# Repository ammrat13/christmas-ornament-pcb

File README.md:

# EE 256 Final Project: Christmas Ornament

Board files and firmware for my final project for EE 256. I made a relatively
simple project - just a smart christmas ornament.

  * Low-light conditions turn on the LEDs
  * Shaking the ornament flashes the NeoPixels
  * Thresholds and flash parameters configurable via micro-SD card
  * Sensor values, activation statistics, and device health visible over
    Bluetooth LE
  * Supports LiIon batteries
  * Watchdog timer for reliability

## Block Diagram

## Project Structure
  * `firmware`: code for the MCU
  * `host`: code to communicate with the MCU over Bluetooth LE
  * `kicad`: board files
  * `kicad-lib`: global library files referenced by the board files

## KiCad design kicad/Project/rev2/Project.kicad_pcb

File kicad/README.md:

# PCB Files

This folder has the KiCad files for the PCBs fabricated. The ADXL 343 Adapter
and Revision 1 of the Project were fabricated. The files in the `kicad-lib`
folder may be needed to edit these files.

## Errata

### Project Revision 1
  * Q1 uses the incorrect footprint. They should be rotated 120 degrees
    counter-clockwise.
  * D2 and D3 don't have decoupling capacitors. They should have 1uF capacitors.
  * D2 doesn't have a decoupling resistor on the data line. It should have a
    470R on the input.

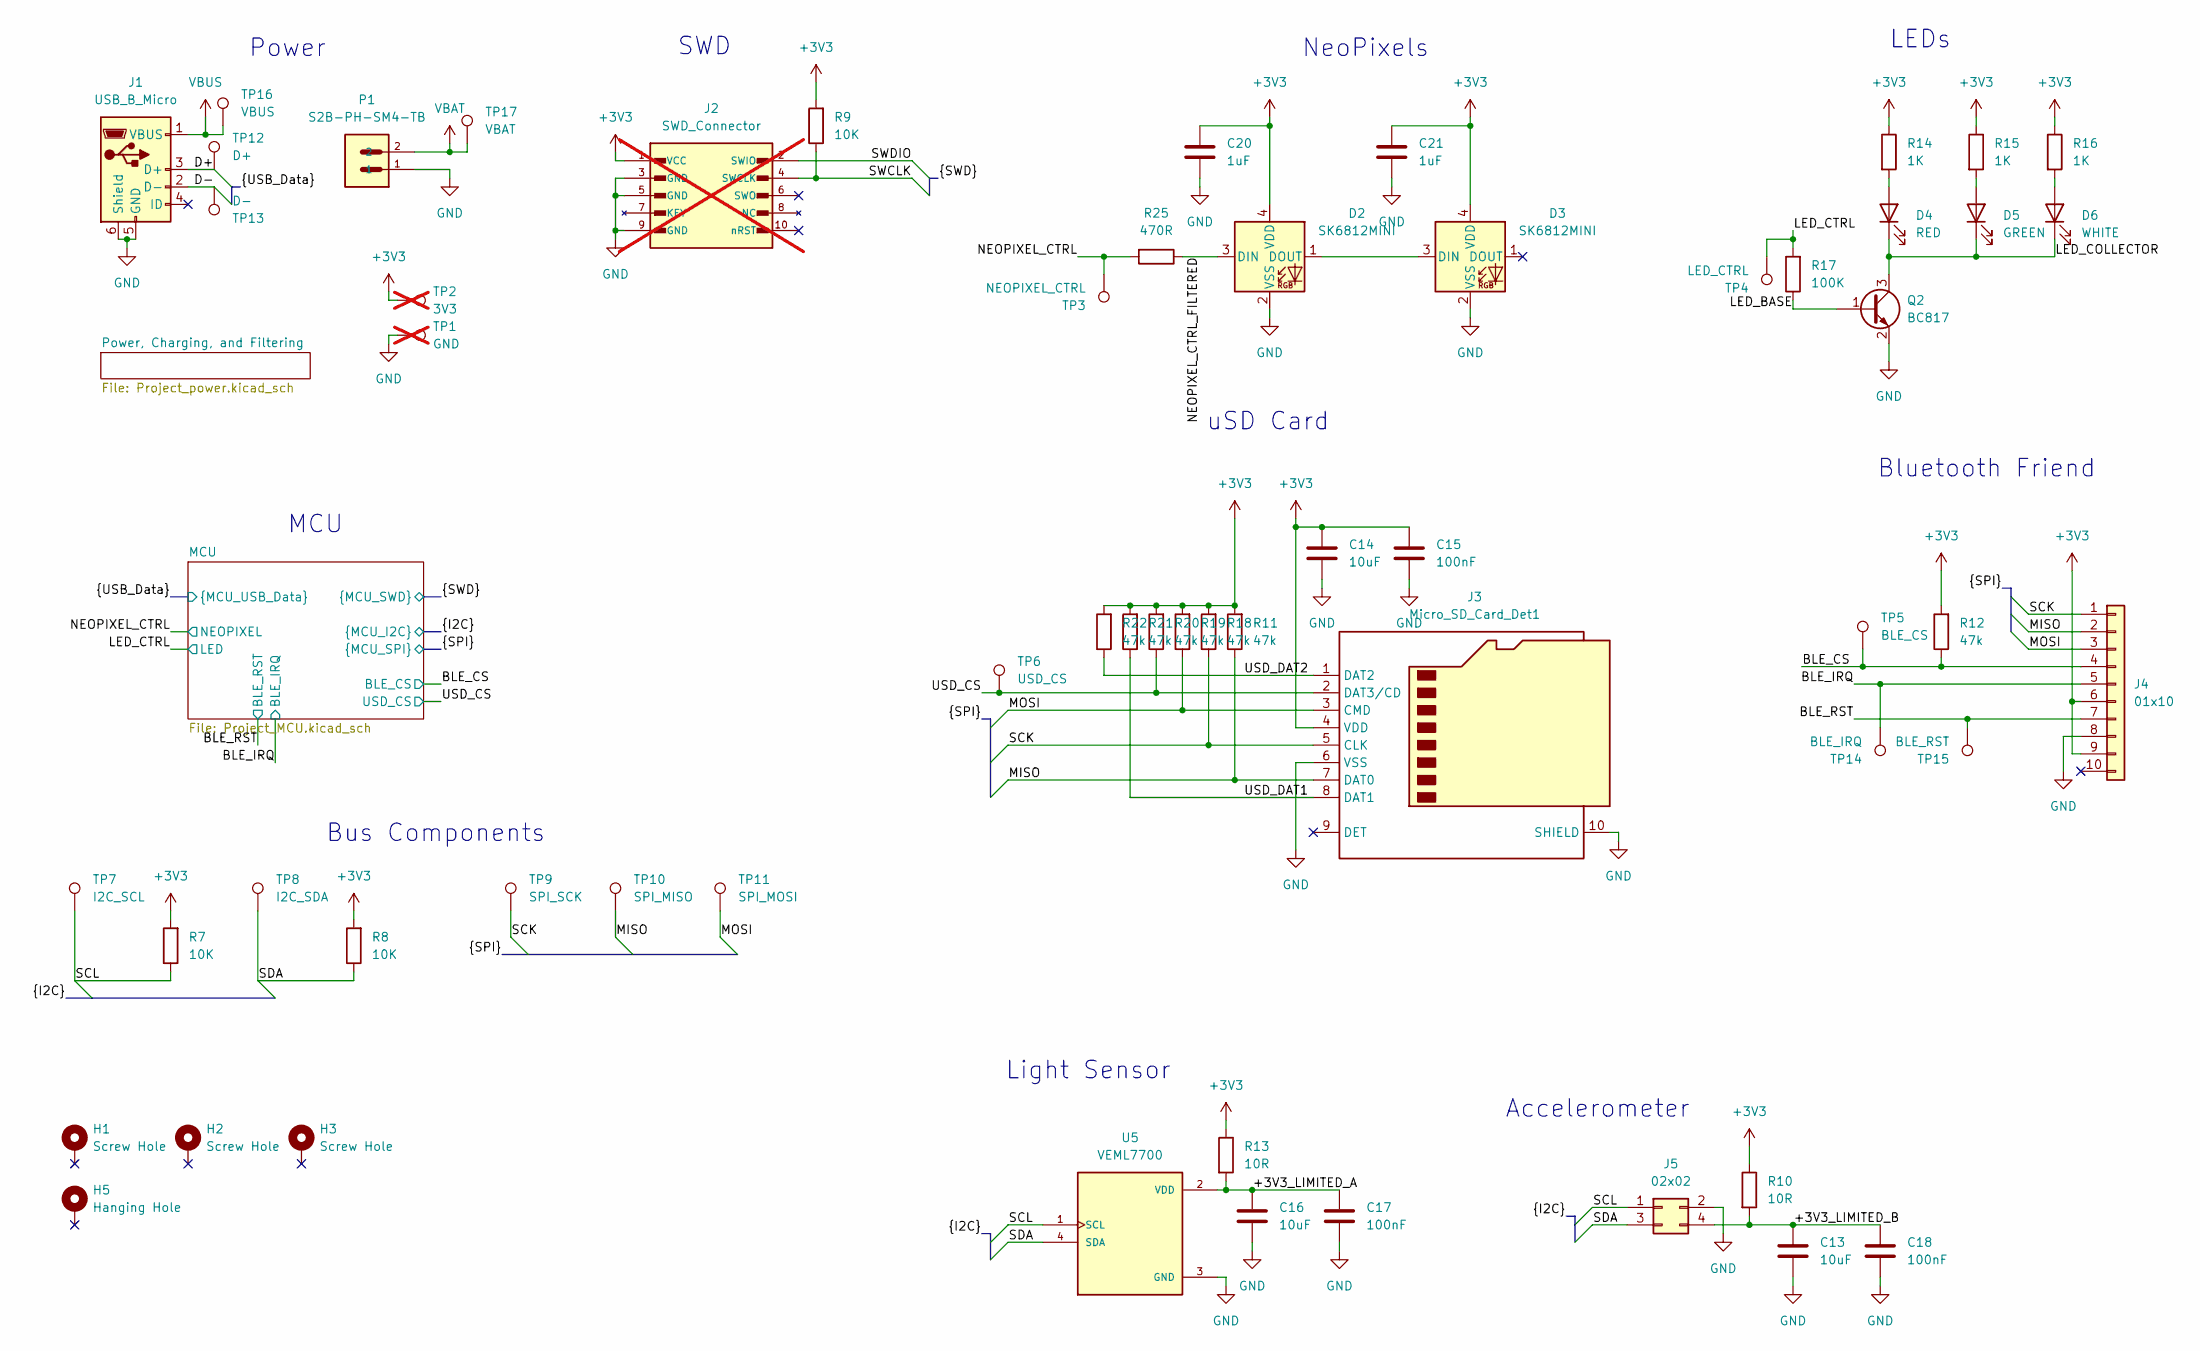
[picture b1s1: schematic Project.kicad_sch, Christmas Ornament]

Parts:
C13, C14, C16: 10uF; C_0805_2012Metric_Pad1.18x1.45mm_HandSolder; Mfr P/N CL21A106KOQNNNE
C15, C17, C18: 100nF; C_0402_1005Metric_Pad0.74x0.62mm_HandSolder; Mfr P/N CL05B104KP5NNNC
C20, C21: 1uF; C_0603_1608Metric_Pad1.08x0.95mm_HandSolder; Mfr P/N CC0603KRX7R7BB105
D2, D3: SK6812MINI; LED_SK6812MINI_PLCC4_3.5x3.5mm_P1.75mm; Mfr P/N 2659
D4: RED; LED_0805_2012Metric_Pad1.15x1.40mm_HandSolder; Mfr P/N LTST-S220KRKT
D5: GREEN; LED_0805_2012Metric_Pad1.15x1.40mm_HandSolder; Mfr P/N LTST-S220KGKT
D6: WHITE; LED_0805_2012Metric_Pad1.15x1.40mm_HandSolder; Mfr P/N LTW-170TK
H1, H2, H3: Screw Hole; MountingHole_3.2mm_M3_DIN965_Pad_TopBottom
H5: Hanging Hole; MountingHole_3.2mm_M3_DIN965_Pad_TopBottom
J1: USB_B_Micro; USB_Micro-B_Amphenol_10103594-0001LF_Horizontal; Mfr P/N 10103594-0001LF
J2: SWD_Connector; CNC_3220-10-0300-00; Mfr P/N 3220-10-0300-00; not fitted
J3: Micro_SD_Card_Det1; GCT_MEM2075-00-140-01-A; Mfr P/N MEM2075-00-140-01-A
J4: 01x10; PinSocket_1x10_P2.54mm_Vertical; Mfr P/N PPTC101LFBN-RC
J5: 02x02; PinSocket_2x02_P2.54mm_Vertical; Mfr P/N PPPC022LFBN-RC
P1: S2B-PH-SM4-TB; JST_PH_S2B-PH-SM4-TB_1x02-1MP_P2.00mm_Horizontal; Mfr P/N S2B-PH-SM4-TB
Q2: BC817; SOT-23; Mfr P/N BC817-25LT1G
R7, R8, R9: 10K; R_0603_1608Metric_Pad0.98x0.95mm_HandSolder; Mfr P/N RNCP0603FTD10K0
R10, R13: 10R; R_0603_1608Metric_Pad0.98x0.95mm_HandSolder; Mfr P/N RMCF0603FT10R0
R11, R12, R18, R19, R20, R21, R22: 47k; R_0603_1608Metric_Pad0.98x0.95mm_HandSolder; Mfr P/N RC0603FR-0747KL
R14, R15, R16: 1K; R_0603_1608Metric_Pad0.98x0.95mm_HandSolder; Mfr P/N MCT06030C1001FP500
R17: 100K; R_0603_1608Metric_Pad0.98x0.95mm_HandSolder; Mfr P/N RMCF0603FT100K
R25: 470R; R_0603_1608Metric_Pad0.98x0.95mm_HandSolder; Mfr P/N RC0603JR-07470RL
TP1: GND; TP_5011; Mfr P/N 5011; not fitted
TP2: 3V3; TP_5011; Mfr P/N 5010; not fitted
TP3: NEOPIXEL_CTRL; TestPoint_Pad_D2.0mm
TP4: LED_CTRL; TestPoint_Pad_D2.0mm
TP5: BLE_CS; TestPoint_Pad_D2.0mm
TP6: USD_CS; TestPoint_Pad_D2.0mm
TP7: I2C_SCL; TestPoint_Pad_D2.0mm
TP8: I2C_SDA; TestPoint_Pad_D2.0mm
TP9: SPI_SCK; TestPoint_Pad_D2.0mm
TP10: SPI_MISO; TestPoint_Pad_D2.0mm
TP11: SPI_MOSI; TestPoint_Pad_D2.0mm
TP12: D+; TestPoint_Pad_D2.0mm
TP13: D-; TestPoint_Pad_D2.0mm
TP14: BLE_IRQ; TestPoint_Pad_D2.0mm
TP15: BLE_RST; TestPoint_Pad_D2.0mm
TP16: VBUS; TestPoint_Pad_D2.0mm
TP17: VBAT; TestPoint_Pad_D2.0mm
U5: VEML7700; XDCR_VEML7700-TR; Mfr P/N VEML7700-TR

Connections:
+3V3: C14.1, C15.1, C20.1, C21.1, D2.4 (VDD), D3.4 (VDD), J2.1 (VCC), J3.4 (VDD), J4.6, J4.9, R7.2, R8.2, R9.2, R10.1, R11.2, R12.2, R13.1, R14.1, R15.1, R16.1, R18.2, R19.2, R20.2, R21.2, R22.2, TP2.1; also elsewhere on the board
/+3V3_LIMITED_A: C16.1, C17.1, R13.2, U5.2 (VDD)
/+3V3_LIMITED_B: C13.1, C18.1, J5.4, R10.2
/BLE_CS: J4.4, R12.1, TP5.1; also elsewhere on the board
/BLE_IRQ: J4.5, TP14.1; also elsewhere on the board
/BLE_RST: J4.7, TP15.1; also elsewhere on the board
/D+: J1.3 (D+), TP12.1; also elsewhere on the board
/D-: J1.2 (D-), TP13.1; also elsewhere on the board
/LED_BASE: Q2.1 (B), R17.1
/LED_COLLECTOR: D4.1 (K), D5.1 (K), D6.1 (K), Q2.3 (C)
/LED_CTRL: R17.2, TP4.1; also elsewhere on the board
/MISO: J3.7 (DAT0), J4.2, R11.1, TP10.1; also elsewhere on the board
/MOSI: J3.3 (CMD), J4.3, R19.1, TP11.1; also elsewhere on the board
/NEOPIXEL_CTRL: R25.2, TP3.1; also elsewhere on the board
/NEOPIXEL_CTRL_FILTERED: D2.3 (DIN), R25.1
/SCK: J3.5 (CLK), J4.1, R18.1, TP9.1; also elsewhere on the board
/SCL: J5.1, R7.1, TP7.1, U5.1 (SCL); also elsewhere on the board
/SDA: J5.3, R8.1, TP8.1, U5.4 (SDA); also elsewhere on the board
/SWCLK: J2.4 (SWCLK), R9.1; also elsewhere on the board
/SWDIO: J2.2 (SWIO); also elsewhere on the board
/USD_CS: J3.2 (DAT3/CD), R20.1, TP6.1; also elsewhere on the board
/USD_DAT1: J3.8 (DAT1), R21.1
/USD_DAT2: J3.1 (DAT2), R22.1
GND: C13.2, C14.2, C15.2, C16.2, C17.2, C18.2, C20.2, C21.2, D2.2 (VSS), D3.2 (VSS), J1.5 (GND), J1.6 (Shield), J2.3 (GND), J2.5 (GND), J2.9 (GND), J3.6 (VSS), J3.10 (SHIELD), J4.8, J5.2, P1.1, Q2.2 (E), TP1.1, U5.3 (GND); also elsewhere on the board
unnamed: D2.1 (DOUT), D3.3 (DIN)
unnamed: D4.2 (A), R14.2
unnamed: D5.2 (A), R15.2
unnamed: D6.2 (A), R16.2
VBAT: P1.2, TP17.1; also elsewhere on the board
VBUS: J1.1 (VBUS), TP16.1; also elsewhere on the board

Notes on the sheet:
MCU
Accelerometer
Bus Components
Bluetooth Friend
SWD
Light Sensor
NeoPixels
uSD Card
LEDs
Power

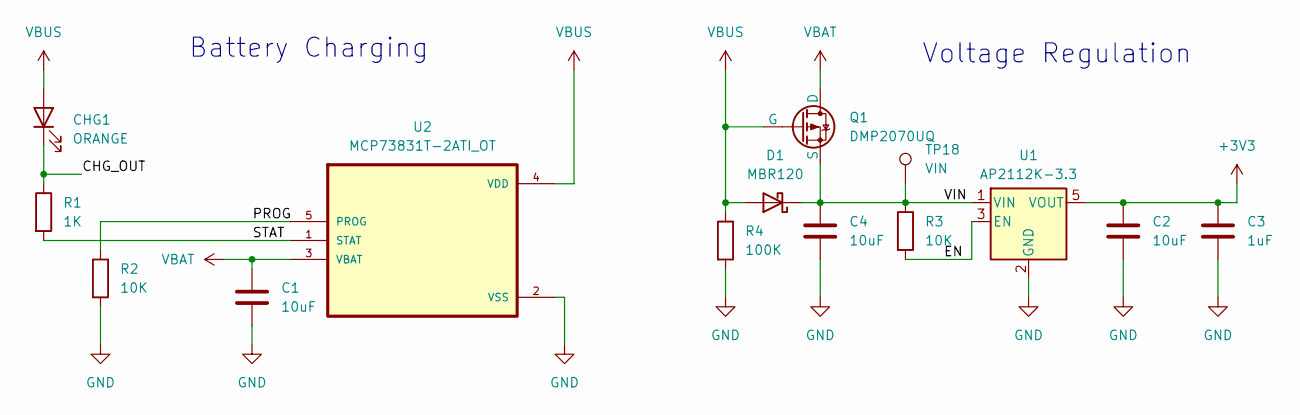
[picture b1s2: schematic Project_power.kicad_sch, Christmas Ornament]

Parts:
C1, C2, C4: 10uF; C_0805_2012Metric_Pad1.18x1.45mm_HandSolder; Mfr P/N CL21A106KOQNNNE
C3: 1uF; C_0603_1608Metric_Pad1.08x0.95mm_HandSolder; Mfr P/N CC0603KRX7R7BB105
CHG1: ORANGE; LED_0805_2012Metric_Pad1.15x1.40mm_HandSolder; Mfr P/N B1701UD--20D000414U1930
D1: MBR120; D_SOD-123; Mfr P/N MBR120LSFT1G
Q1: DMP2070UQ; SOT-23_Handsoldering
R1: 1K; R_0603_1608Metric_Pad0.98x0.95mm_HandSolder; Mfr P/N MCT06030C1001FP500
R2, R3: 10K; R_0603_1608Metric_Pad0.98x0.95mm_HandSolder; Mfr P/N RNCP0603FTD10K0
R4: 100K; R_0603_1608Metric_Pad0.98x0.95mm_HandSolder; Mfr P/N RMCF0603FT100K
TP18: VIN; TestPoint_Pad_D2.0mm
U1: AP2112K-3.3; SOT-23-5
U2: MCP73831T-2ATI_OT; SOT-23-5_HandSoldering; Mfr P/N MCP73831T-2ATI/OT

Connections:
+3V3: C2.1, C3.1, U1.5 (VOUT); also elsewhere on the board
/Power, Charging, and Filtering/CHG_OUT: CHG1.1 (K), R1.1
/Power, Charging, and Filtering/EN: R3.2, U1.3 (EN)
/Power, Charging, and Filtering/PROG: R2.1, U2.5 (PROG)
/Power, Charging, and Filtering/STAT: R1.2, U2.1 (STAT)
/Power, Charging, and Filtering/VIN: C4.1, D1.1 (K), Q1.2 (S), R3.1, TP18.1, U1.1 (VIN)
GND: C1.2, C2.2, C3.2, C4.2, R2.2, R4.2, U1.2 (GND), U2.2 (VSS); also elsewhere on the board
VBAT: C1.1, Q1.3 (D), U2.3 (VBAT); also elsewhere on the board
VBUS: CHG1.2 (A), D1.2 (A), Q1.1 (G), R4.1, U2.4 (VDD); also elsewhere on the board

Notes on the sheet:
Battery Charging
Voltage Regulation

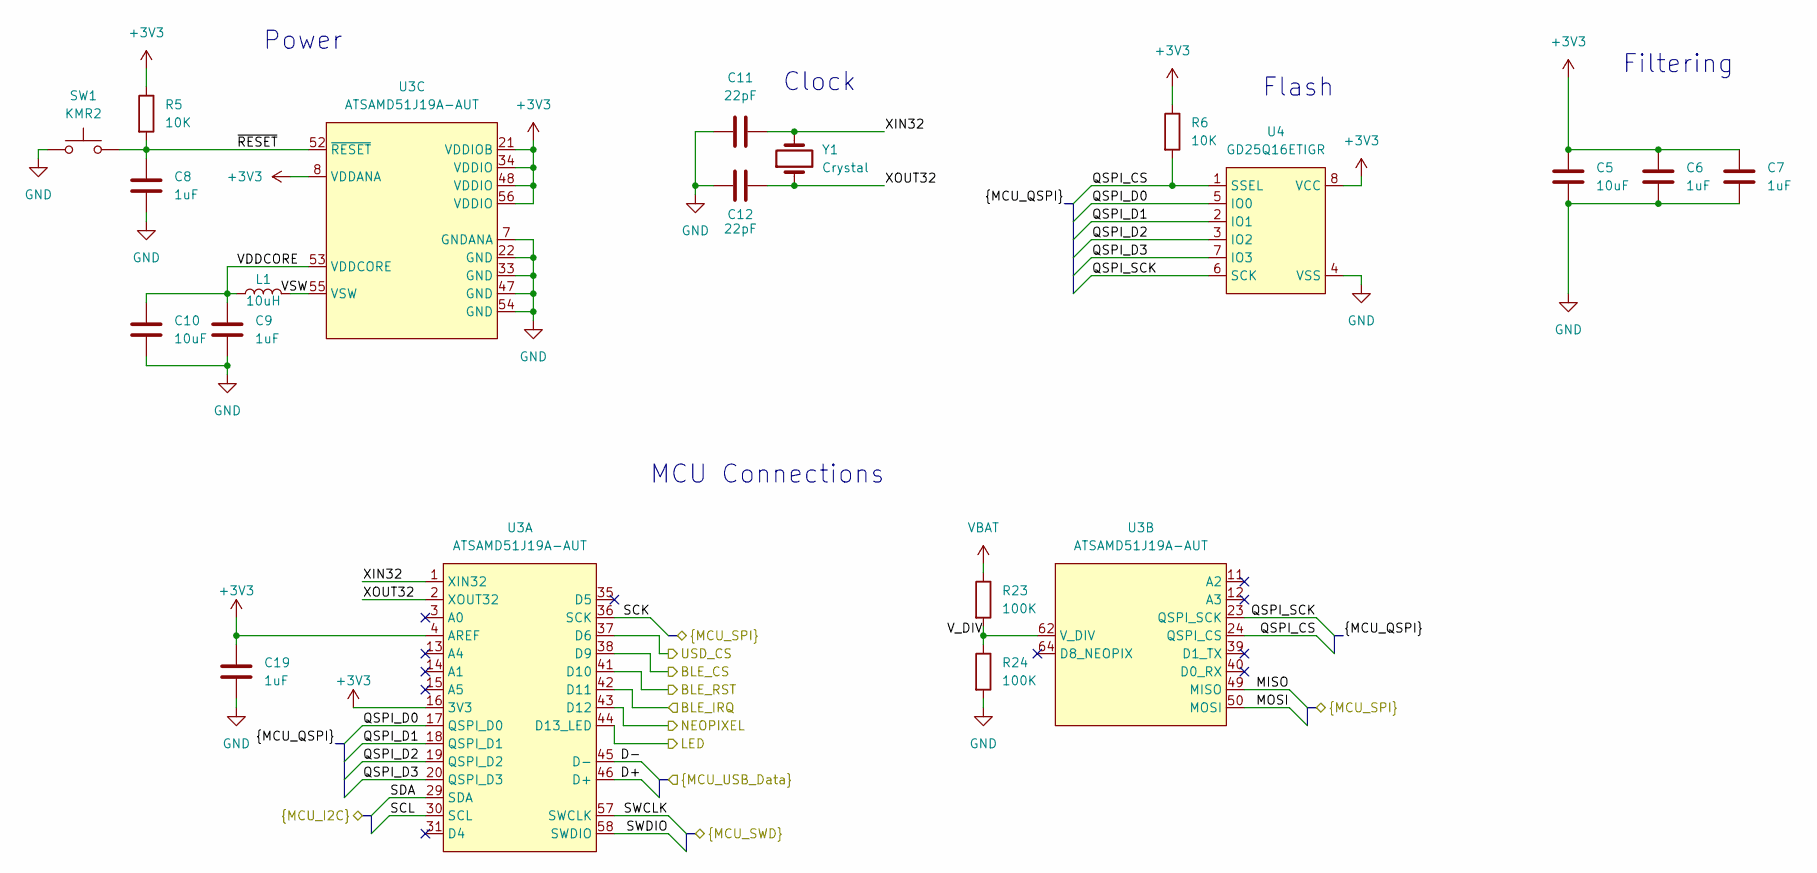
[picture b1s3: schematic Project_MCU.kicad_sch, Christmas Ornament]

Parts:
C5, C10: 10uF; C_0805_2012Metric_Pad1.18x1.45mm_HandSolder; Mfr P/N CL21A106KOQNNNE
C6, C7, C8, C9, C19: 1uF; C_0603_1608Metric_Pad1.08x0.95mm_HandSolder; Mfr P/N CC0603KRX7R7BB105
C11, C12: 22pF; C_0603_1608Metric_Pad1.08x0.95mm_HandSolder; Mfr P/N C0603C220K4GAC7867
L1: 10uH; L_1008_2520Metric; Mfr P/N LSQEA251818T100K
R5, R6: 10K; R_0603_1608Metric_Pad0.98x0.95mm_HandSolder; Mfr P/N RNCP0603FTD10K0
R23, R24: 100K; R_0603_1608Metric_Pad0.98x0.95mm_HandSolder; Mfr P/N RMCF0603FT100K
SW1: KMR2; SW_Push_1P1T_NO_CK_KMR2; Mfr P/N KMR241NG ULC LFS
U3: ATSAMD51J19A-AUT; TQFP-64_10x10mm_P0.5mm; Mfr P/N ATSAMD51J19A-AUT
U4: GD25Q16ETIGR; SOIC-8_3.9x4.9mm_P1.27mm; Mfr P/N GD25Q16ETIGR
Y1: Crystal; XTAL3215; Mfr P/N STDMUA17-32.768K

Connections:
+3V3: C5.1, C6.1, C7.1, C19.1, R5.1, R6.1, U3.4 (AREF), U3.8 (VDDANA), U3.16 (3V3), U3.21 (VDDIOB), U3.34 (VDDIO), U3.48 (VDDIO), U3.56 (VDDIO), U4.8 (VCC); also elsewhere on the board
/BLE_CS: U3.38 (D9); also elsewhere on the board
/BLE_IRQ: U3.42 (D11); also elsewhere on the board
/BLE_RST: U3.41 (D10); also elsewhere on the board
/D+: U3.46 (D+); also elsewhere on the board
/D-: U3.45 (D-); also elsewhere on the board
/LED_CTRL: U3.44 (D13_LED); also elsewhere on the board
/MCU/QSPI_CS: R6.2, U3.24 (QSPI_CS), U4.1 (SSEL)
/MCU/QSPI_D0: U3.17 (QSPI_D0), U4.5 (IO0)
/MCU/QSPI_D1: U3.18 (QSPI_D1), U4.2 (IO1)
/MCU/QSPI_D2: U3.19 (QSPI_D2), U4.3 (IO2)
/MCU/QSPI_D3: U3.20 (QSPI_D3), U4.7 (IO3)
/MCU/QSPI_SCK: U3.23 (QSPI_SCK), U4.6 (SCK)
/MCU/VDDCORE: C9.1, C10.1, L1.1, U3.53 (VDDCORE)
/MCU/VSW: L1.2, U3.55 (VSW)
/MCU/V_DIV: R23.2, R24.1, U3.62 (V_DIV)
/MCU/XIN32: C11.1, U3.1 (XIN32), Y1.2
/MCU/XOUT32: C12.1, U3.2 (XOUT32), Y1.1
/MCU/~RESET: C8.1, R5.2, SW1.2, U3.52 (~RESET)
/MISO: U3.49 (MISO); also elsewhere on the board
/MOSI: U3.50 (MOSI); also elsewhere on the board
/NEOPIXEL_CTRL: U3.43 (D12); also elsewhere on the board
/SCK: U3.36 (SCK); also elsewhere on the board
/SCL: U3.30 (SCL); also elsewhere on the board
/SDA: U3.29 (SDA); also elsewhere on the board
/SWCLK: U3.57 (SWCLK); also elsewhere on the board
/SWDIO: U3.58 (SWDIO); also elsewhere on the board
/USD_CS: U3.37 (D6); also elsewhere on the board
GND: C5.2, C6.2, C7.2, C8.2, C9.2, C10.2, C11.2, C12.2, C19.2, R24.2, SW1.1, U3.7 (GNDANA), U3.22 (GND), U3.33 (GND), U3.47 (GND), U3.54 (GND), U4.4 (VSS); also elsewhere on the board
VBAT: R23.1; also elsewhere on the board

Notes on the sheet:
Power
Filtering
Clock
MCU Connections
Flash

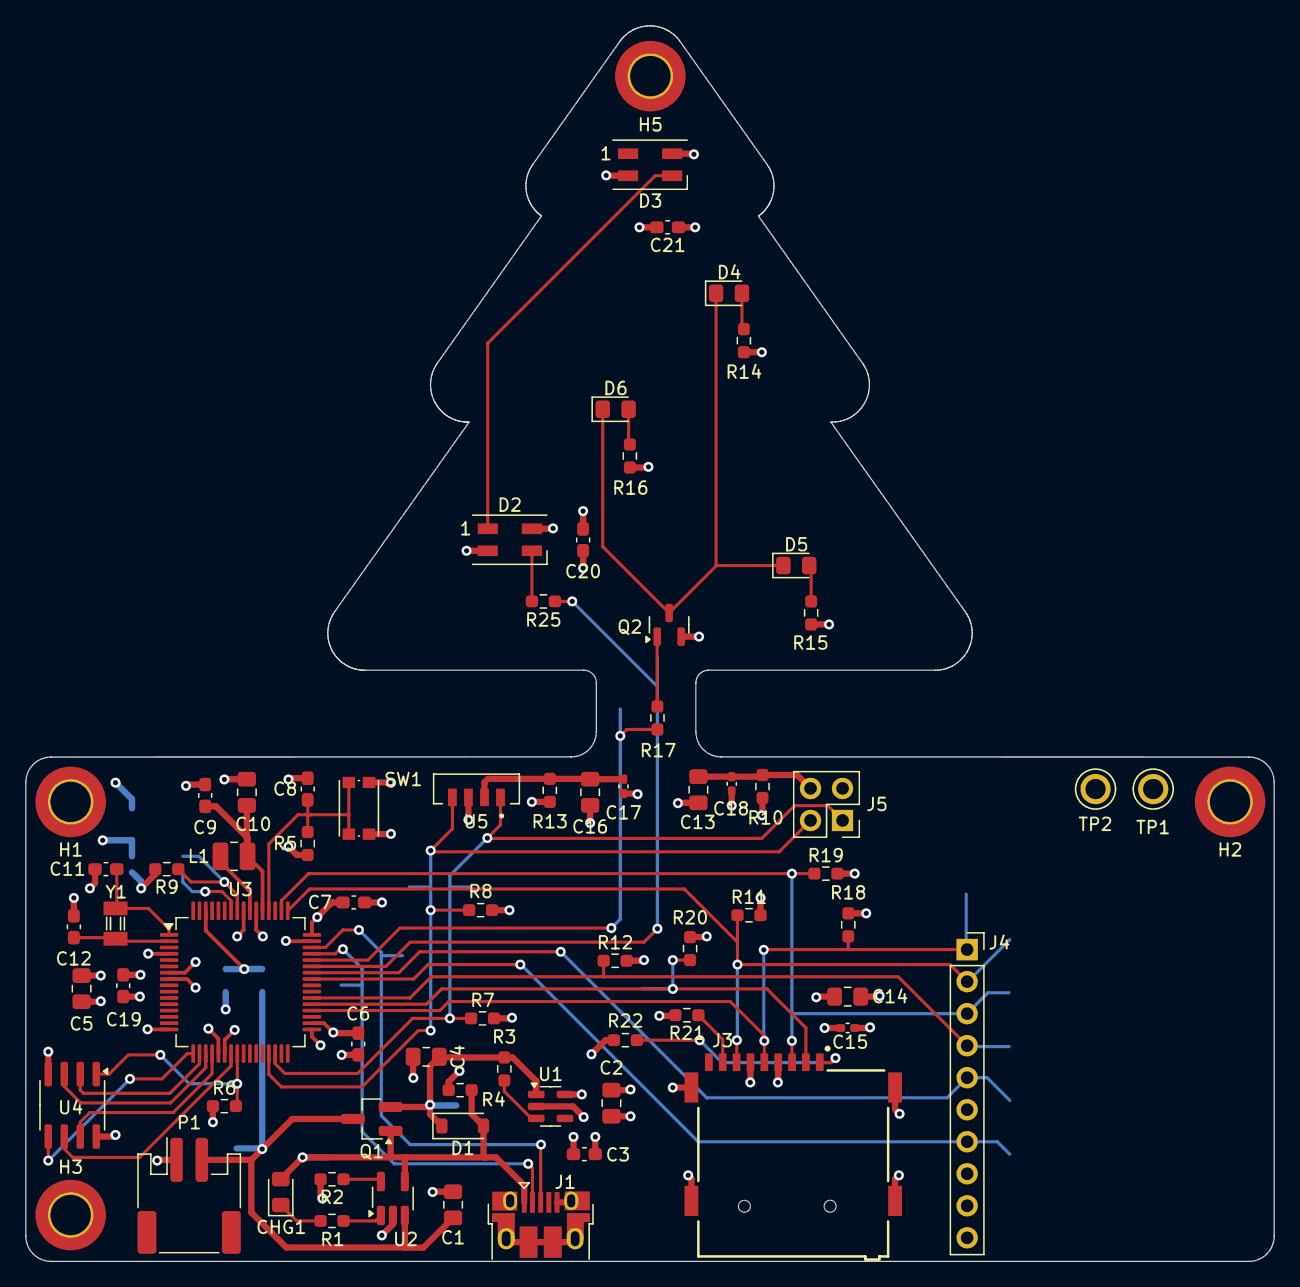
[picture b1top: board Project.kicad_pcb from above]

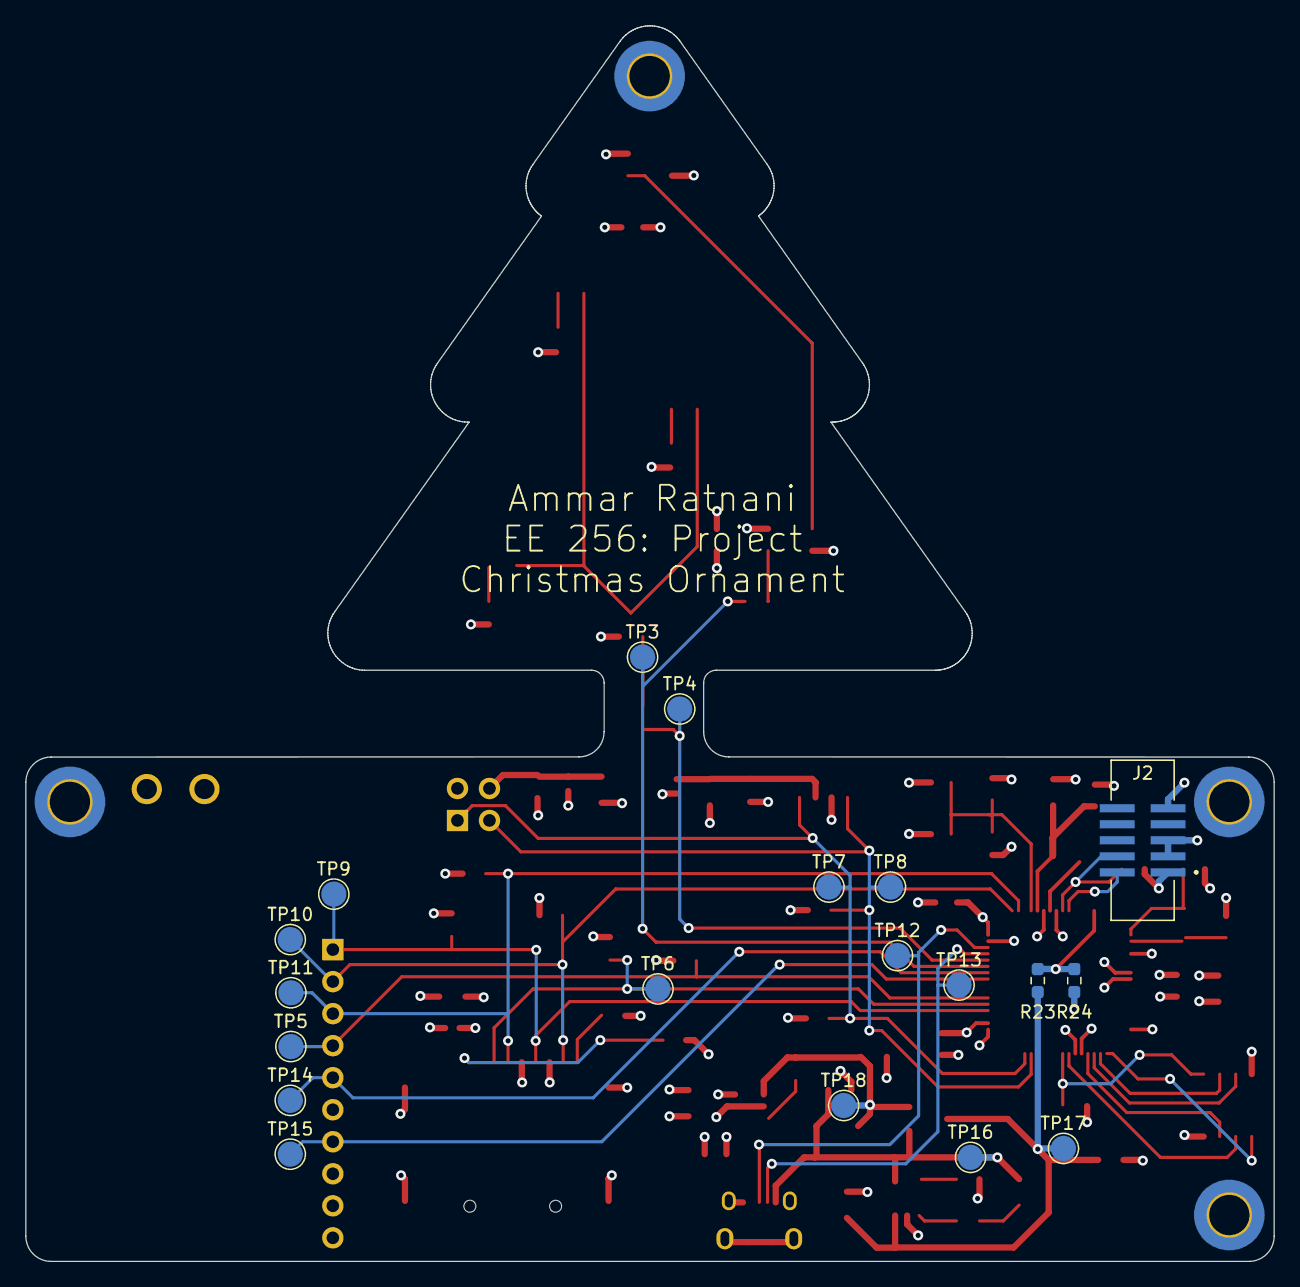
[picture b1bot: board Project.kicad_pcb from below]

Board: 4 copper layers, 99.0 x 98.0 mm, 91 parts (19 on the bottom side), 47 nets.

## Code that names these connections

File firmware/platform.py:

"""
Classes for all the peripherals on the PCB.

Importing this file will also run the platform initialization code, which just
mounts the SD card and resets the bluetooth module. This should be the first
thing imported in `code.py`.
"""

import adafruit_adxl34x
import adafruit_sdcard
import adafruit_veml7700
import analogio
import board
import busio
import digitalio
import neopixel
import storage

import driver.bluefruitspi

# Pins
LED_PIN = board.D13
NEOPIXEL_PIN = board.D12
BATTERY_PIN = board.BATTERY
USD_CS_PIN = board.D6
BLE_CS_PIN = board.D9
BLE_RST_PIN = board.D10
BLE_IRQ_PIN = board.D11

# Busses
SPI_BUS = busio.SPI(board.SCK, MOSI=board.MOSI, MISO=board.MISO)
I2C_BUS = busio.I2C(board.SCL, board.SDA)

# LED
LED = digitalio.DigitalInOut(LED_PIN)
LED.direction = digitalio.Direction.OUTPUT
# NeoPixel
NEOPIXEL_LEN = 2
NEOPIXEL = neopixel.NeoPixel(NEOPIXEL_PIN, 2, auto_write=False)
# Battery
BATTERY = analogio.AnalogIn(BATTERY_PIN)

# I2C Peripherals
LIGHT_SENSOR = adafruit_veml7700.VEML7700(I2C_BUS)
ACCELEROMETER = adafruit_adxl34x.ADXL343(I2C_BUS, address=0x1d)

# microSD Card. This has to be initialized before the bluetooth module since the
# SPI bus is shared between them. The documentation says not doing so messes
# with the initialization of the microSD card.
USD_CS = digitalio.DigitalInOut(USD_CS_PIN)
USD = adafruit_sdcard.SDCard(SPI_BUS, USD_CS)
USD_VFS = storage.VfsFat(USD)
storage.mount(USD_VFS, "/sd")

# Bluetooth Module
BLE_CS = digitalio.DigitalInOut(BLE_CS_PIN)
BLE_RST = digitalio.DigitalInOut(BLE_RST_PIN)
BLE_IRQ = digitalio.DigitalInOut(BLE_IRQ_PIN)
BLE = driver.bluefruitspi.BluefruitSPI(SPI_BUS, BLE_CS, BLE_IRQ, BLE_RST)
BLE.init()
BLE.command_check_OK(b"ATZ")

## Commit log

2024-11-21 Modify title blocks for Rev1
2024-11-21 Fix ignore files
2024-11-21 Push Rev2
    This revision fixes the issue with Q1 in Rev1
2024-11-21 Add firmware requirements
2024-11-21 Add basic `README`
2024-11-22 Add discovered errata
2024-11-22 Use the more common NeoPixels
2024-11-28 Add logging and `circup`
2024-11-28 Handle configuration file
2024-11-28 Remove typing
2024-11-28 Refactor into method
2024-11-28 Add BLE
2024-11-28 Fix bugs
2024-11-28 Add tasks code
2024-11-28 Add heap monitor
2024-11-28 Add battery monitor
2024-11-29 Set initial values on boot
2024-11-29 Add async methods to BLE
2024-11-29 Use floats
2024-11-29 Add light sensing code
2024-11-29 Add MIT license
2024-11-29 Rename
2024-11-29 Preliminary NeoPixel code
2024-11-29 Change `get` and `set`
2024-11-29 Fix global variable
2024-11-29 Tune NeoPixel
2024-11-29 Add `Makefile`
2024-11-29 Tweak `Makefile`
2024-11-29 Change default value
2024-11-29 Copy config over
2024-11-29 Change default
2024-11-30 Change to envvar
2024-11-30 Add firmware build instructions
2024-11-30 Add `host` folder
2024-11-30 Start BLE code
2024-11-30 Architect requests
2024-11-30 Remove `dead_code`
2024-11-30 Be able to read the heap free
2024-11-30 Add accelerometer count
2024-11-30 Add special case for all `f`s
2024-11-30 Add scaled values
2024-11-30 Minor syntax changes
2024-12-01 Add `feature` for MacOS
2024-12-01 Change units for acceleration threshold
2024-12-01 Add `delay_start`
2024-12-01 Fix typo
2024-12-01 Add read and write characteristics
2024-12-01 Add threshold characteristics
2024-12-01 Handle light characteristics
2024-12-01 Add LED reconfiguration
2024-12-01 Add characteristic writing
2024-12-01 Clippy
2024-12-01 Change length of light threshold
2024-12-01 Update host code
2024-12-01 Fixup default values
2024-12-01 Add neopixel reconfiguration
2024-12-01 Add boot count
2024-12-01 Make the entrypoint compiled
2024-12-01 Add watchdog parameters
2024-12-01 Update default in code
2024-12-01 Add watchdog pet task
2024-12-01 Fixup watchdog
2024-12-01 Add disconnect detection
2024-12-01 Update block diagram
2024-12-01 Add host code `README`
2024-12-01 Add project features
2024-12-01 Add blurb on configuration
2024-12-01 Add check for regular file
2024-12-01 Remove `CFG_RESET_BLE`
2024-12-01 Add device name option
2024-12-02 Add Ctrl-C
